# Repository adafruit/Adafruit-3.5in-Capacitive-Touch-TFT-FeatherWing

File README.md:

## Adafruit TFT FeatherWing - 3.5" 480x320 Capacitive Touchscreen - STEMMA QT / Qwiic PCB

<a href="http://www.adafruit.com/products/5872"><br/>
Click here to purchase one from the Adafruit shop</a>

PCB files for the Adafruit TFT FeatherWing - 3.5" 480x320 Capacitive Touchscreen - STEMMA QT / Qwiic. 

Format is EagleCAD schematic and board layout
* https://www.adafruit.com/product/5872

### Description

Bedeck your Feather project with a beautiful Adafruit TFT FeatherWing, 3.5" 480x320 Capacitive Touchscreen. This TFT display is 3.5" diagonal with a bright white-LED backlight and a built-in microSD card socket. You get a massive 480x320 pixels with individual 16-bit color pixel control. It has way more resolution than a black and white 128x64 display, and twice as much as our 2.4" TFT FeatherWing. As a bonus, this display comes with a multi-touch capacitive touchscreen attached to it already, so you can detect up to 5 finger presses anywhere on the screen

This FeatherWing uses a SPI display and SD card socket, with I2C touchscreen. It works with any and all Feather boards but given the large display it works best with our faster boards like the nRF52, RP2040, ESP32, M0 and M4 (basically anything that is > 32 MHz). It includes a capacitive touchscreen controller controlled over I2C so you only need one additional interrupt pin to add a high quality touchscreen controller. One more pin is used for an optional SD card that can be used for storing images for display.

This Wing comes fully assembled with dual sockets for your Feather to plug into. You get two sockets per pin, so you can plug in wires if you want to connect to Feather pins. Alternatively, each pin has a large square pad on the PCB for direct soldering.

The TFT display is an HX8357D-chipset compatible, we have both Arduino and CircuitPython libraries for it. And the capacitive touch driver is FT5336, with 5-point multi-touch, with both Arduino and CircuitPython libraries as well.

Get started in a jiffy with our handy tutorial guide which has code, schematics, libraries, and examples for anything you'd like to do!

### License

Adafruit invests time and resources providing this open source design, please support Adafruit and open-source hardware by purchasing products from [Adafruit](https://www.adafruit.com)!

Designed by Limor Fried/Ladyada for Adafruit Industries.

Creative Commons Attribution/Share-Alike, all text above must be included in any redistribution. 
See license.txt for additional details.

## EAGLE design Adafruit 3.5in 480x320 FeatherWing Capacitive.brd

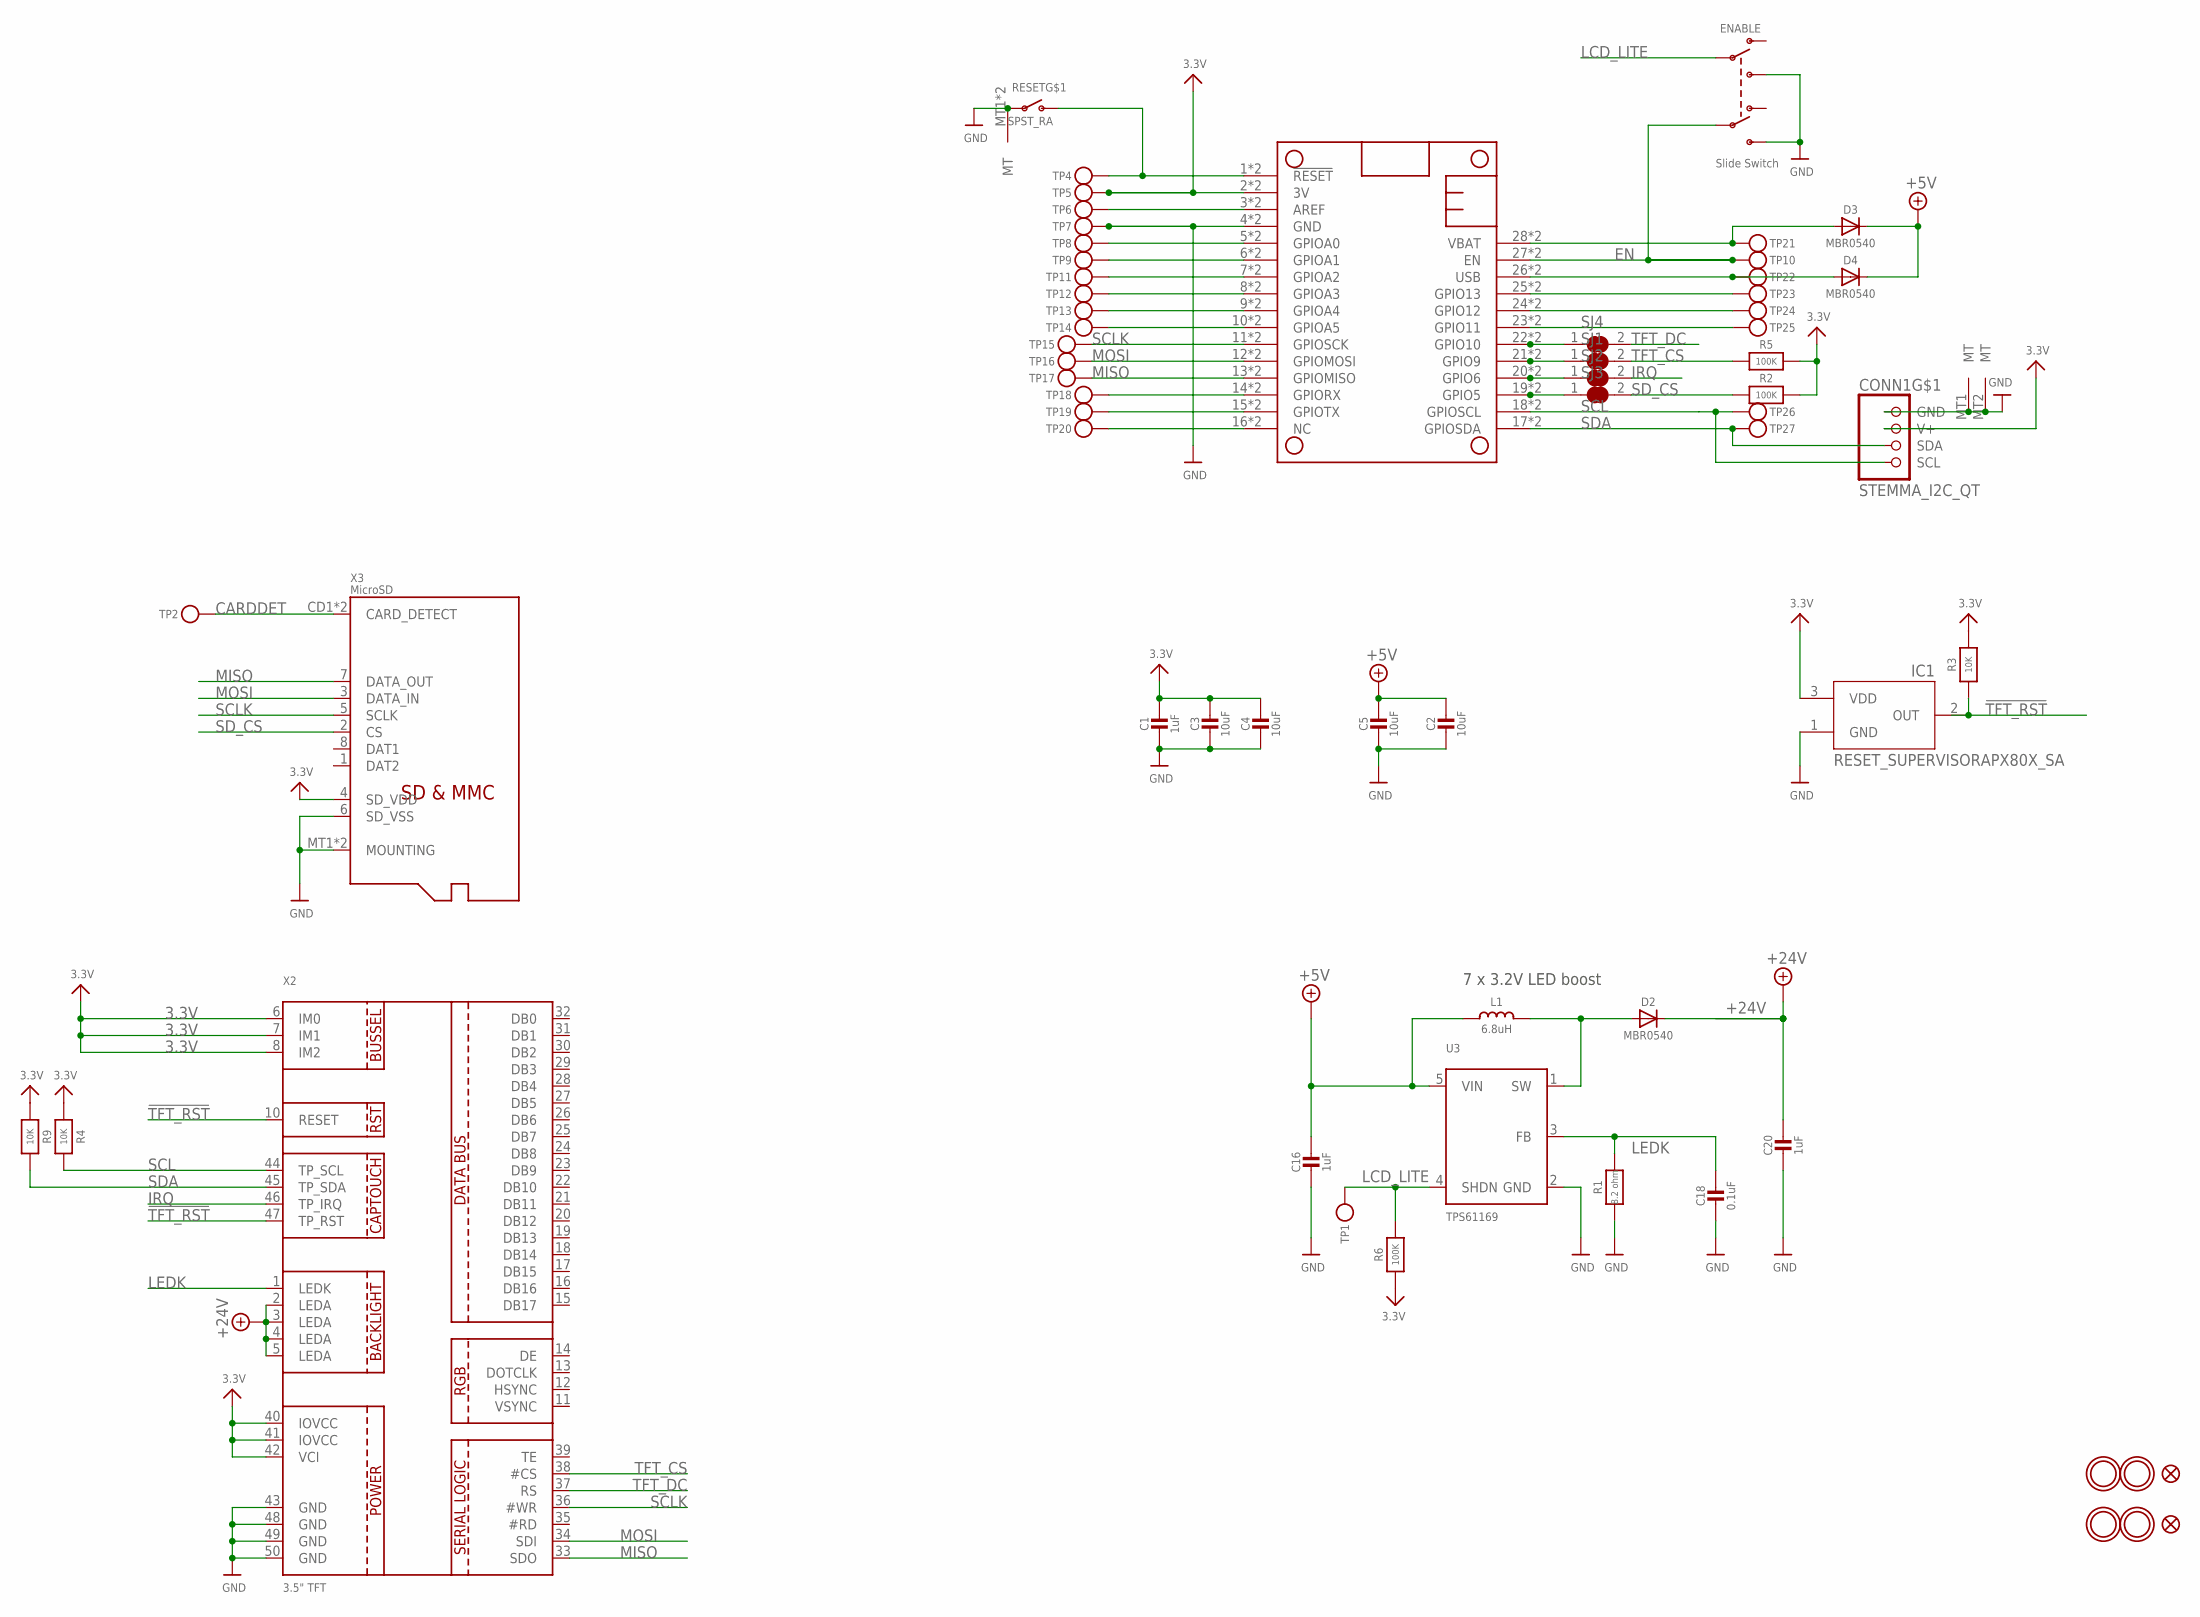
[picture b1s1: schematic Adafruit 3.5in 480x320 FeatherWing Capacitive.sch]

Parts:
C1, C16, C20: 1uF; 0805-NO
C2, C3, C4, C5: 10uF; 0805-NO
C18: 0.1uF; 0603-NO
CONN1: STEMMA_I2C_QT; JST_SH4
D2, D3, D4: MBR0540; SOD-123
ENABLE: Slide Switch; EG1390
IC1: RESET_SUPERVISORAPX80X_SA; SOT23-WIDE
L1: 6.8uH; INDUCTOR_5X5MM_NR5040_NOTHERMALS
MS2: FEATHERWING_SMTDUAL; FEATHERWING_SMT2
R1: 8.2 ohm; 0603-NO
R2, R5, R6: 100K; 0603-NO
R3, R4, R9: 10K; 0603-NO
RESET: SPST_RA; SPST_TACTILE_RA
SJ1, SJ2, SJ3, SJ4: SOLDERJUMPER_CLOSED; SOLDERJUMPER_CLOSEDWIRE
TP1, TP2, TP4, TP5, TP6, TP7, TP8, TP9, TP10, TP11, TP12, TP13, TP14, TP15, TP16, TP17, TP18, TP19, TP20, TP21, TP22, TP23, TP24, TP25, TP26, TP27: TESTPOINTPAD2MM; TESTPOINT_PAD_2MM
U3: TPS61169; SC70-5
U$7, U$15, U$16, U$17: MOUNTINGHOLE3.0THIN; MOUNTINGHOLE_3.0_PLATEDTHIN
U$9, U$23: FIDUCIAL_1MM
X2: 3.5" TFT; TFT_3.5IN_320X480_50PIN
X3: MicroSD; MICROSD

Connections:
3.3V: C1.1, C3.1, C4.1, CONN1.2 (V+), IC1.3 (VDD), MS2.2 (3V), MS2.2' (3V), R2.2, R3.2, R4.1, R5.2, R6.1, R9.1, TP5.P$1, X2.6 (IM0), X2.7 (IM1), X2.8 (IM2), X2.40 (IOVCC), X2.41 (IOVCC), X2.42 (VCI), X3.4 (SD_VDD)
!RESET: MS2.1 (!RESET), MS2.1' (!RESET), RESET.2 (S), TP4.P$1
!TFT_RST: IC1.2 (OUT), R3.1, X2.10 (RESET), X2.47 (TP_RST)
+5V: C2.1, C5.1, C16.1, D3.C, D4.C, L1.P$1 (1), U3.5 (VIN)
+24V: C20.1, D2.C, X2.2 (LEDA), X2.3 (LEDA), X2.4 (LEDA), X2.5 (LEDA)
A: MS2.5 (GPIOA0), MS2.5' (GPIOA0), TP8.P$1
AREF: MS2.3 (AREF), MS2.3' (AREF), TP6.P$1
B: MS2.6 (GPIOA1), MS2.6' (GPIOA1), TP9.P$1
C: MS2.7 (GPIOA2), MS2.7' (GPIOA2), TP11.P$1
CARDDET: TP2.P$1, X3.CD1 (CARD_DETECT), X3.CD2 (CARD_DETECT)
D: MS2.8 (GPIOA3), MS2.8' (GPIOA3), TP12.P$1
E: MS2.9 (GPIOA4), MS2.9' (GPIOA4), TP13.P$1
EN: ENABLE.P2, MS2.27 (EN), MS2.27' (EN), TP10.P$1
F: MS2.10 (GPIOA5), MS2.10' (GPIOA5), TP14.P$1
G: MS2.16 (NC), MS2.16' (NC), TP20.P$1
GND: C1.2, C2.2, C3.2, C4.2, C5.2, C16.2, C18.2, C20.2, CONN1.1 (GND), CONN1.MT1 (MT), CONN1.MT2 (MT), ENABLE.S1, ENABLE.S2, IC1.1 (GND), MS2.4 (GND), MS2.4' (GND), R1.1, RESET.1, RESET.MT1 (MT), RESET.MT2 (MT), TP7.P$1, U3.2 (GND), X2.43 (GND), X2.48 (GND), X2.49 (GND), X2.50 (GND), X3.6 (SD_VSS), X3.MT1 (MOUNTING), X3.MT2 (MOUNTING)
H: MS2.19 (GPIO5), MS2.19' (GPIO5), SJ3.1
I: MS2.20 (GPIO6), MS2.20' (GPIO6), SJ2.1
IRQ: SJ2.2, X2.46 (TP_IRQ)
J: MS2.21 (GPIO9), MS2.21' (GPIO9), SJ1.1
K: MS2.22 (GPIO10), MS2.22' (GPIO10), SJ4.1
L: MS2.23 (GPIO11), MS2.23' (GPIO11), TP25.P$1
LCD_LITE: ENABLE.P1, R6.2, TP1.P$1, U3.4 (SHDN)
LEDK: C18.1, R1.2, U3.3 (FB), X2.1 (LEDK)
M: MS2.24 (GPIO12), MS2.24' (GPIO12), TP24.P$1
MISO: MS2.13 (GPIOMISO), MS2.13' (GPIOMISO), TP17.P$1, X2.33 (SDO), X3.7 (DATA_OUT)
MOSI: MS2.12 (GPIOMOSI), MS2.12' (GPIOMOSI), TP16.P$1, X2.34 (SDI), X3.3 (DATA_IN)
N: MS2.25 (GPIO13), MS2.25' (GPIO13), TP23.P$1
unnamed: D2.A, L1.P$2 (2), U3.1 (SW)
RX: MS2.14 (GPIORX), MS2.14' (GPIORX), TP18.P$1
SCL: CONN1.4 (SCL), MS2.18 (GPIOSCL), MS2.18' (GPIOSCL), R4.2, TP26.P$1, X2.44 (TP_SCL)
SCLK: MS2.11 (GPIOSCK), MS2.11' (GPIOSCK), TP15.P$1, X2.36 (#WR), X3.5 (SCLK)
SDA: CONN1.3 (SDA), MS2.17 (GPIOSDA), MS2.17' (GPIOSDA), R9.2, TP27.P$1, X2.45 (TP_SDA)
SD_CS: R2.1, SJ3.2, X3.2 (CS)
TFT_CS: R5.1, SJ1.2, X2.38 (#CS)
TFT_DC: SJ4.2, X2.37 (RS)
TX: MS2.15 (GPIOTX), MS2.15' (GPIOTX), TP19.P$1
USB: D4.A, MS2.26 (USB), MS2.26' (USB), TP22.P$1
VBAT: D3.A, MS2.28 (VBAT), MS2.28' (VBAT), TP21.P$1

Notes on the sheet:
7 x 3.2V LED boost

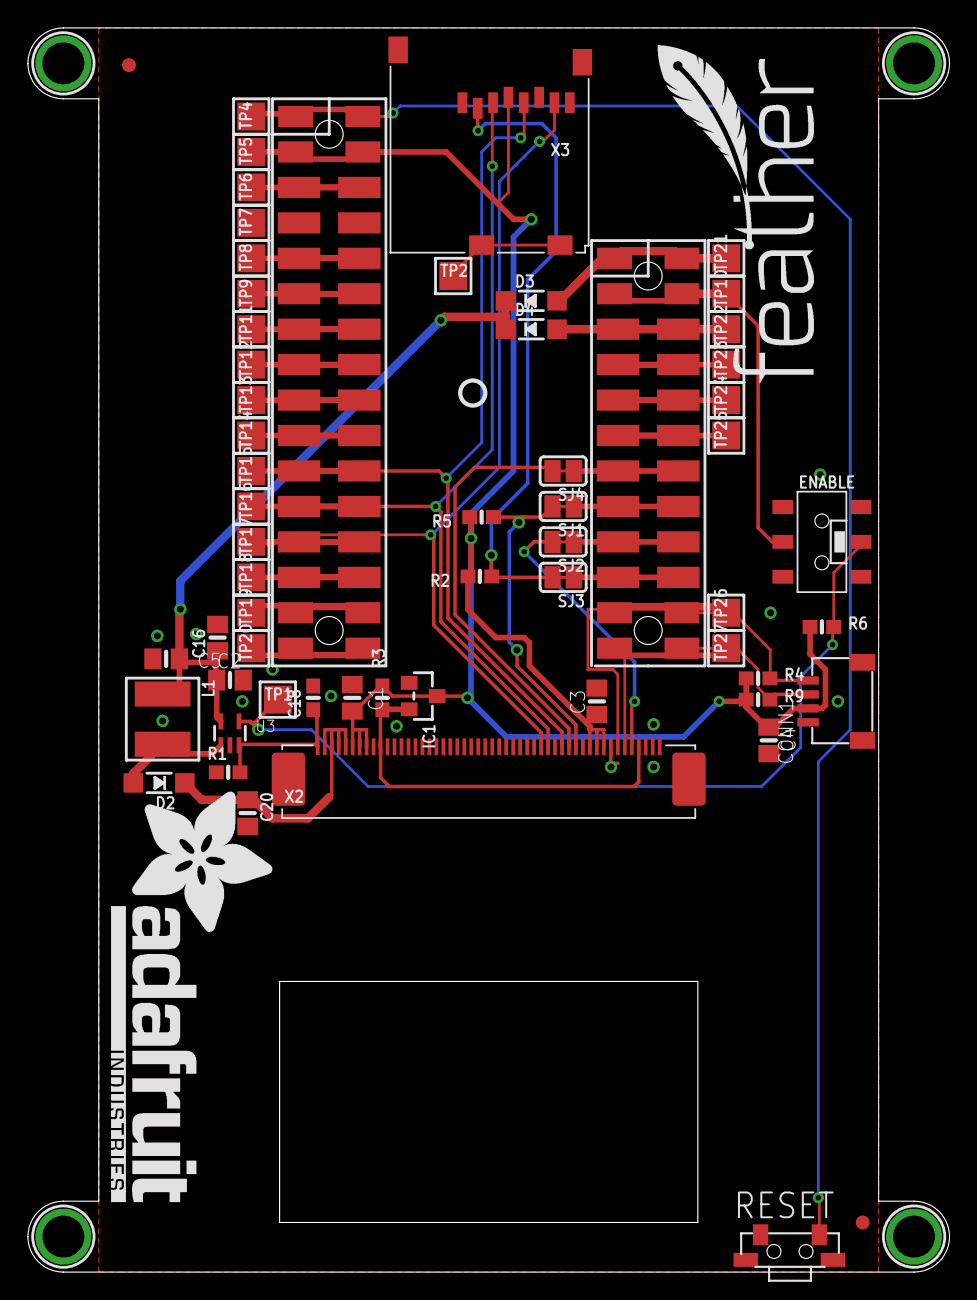
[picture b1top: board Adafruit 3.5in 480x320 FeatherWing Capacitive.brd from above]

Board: 2 copper layers, 66.0 x 89.2 mm, 80 parts (1 on the bottom side), 39 nets.

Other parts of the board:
PLABEL0: PLABEL0
PLABEL1: PLABEL1
PLABEL2: PLABEL2
PLABEL3: PLABEL3
PLABEL4: PLABEL4
PLABEL5: PLABEL5
PLABEL6: PLABEL6
PLABEL7: PLABEL7
PLABEL8: PLABEL8
PLABEL9: PLABEL9
PLABEL12: PLABEL12
PLABEL14: PLABEL14
PLABEL15: PLABEL15
PLABEL16: PLABEL16
U$11: FEATHERLOGO
U$19: ADAFRUIT_TEXT_30MM
U$37: PCBFEAT-REV-040

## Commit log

2024-01-11 cookiecutter
